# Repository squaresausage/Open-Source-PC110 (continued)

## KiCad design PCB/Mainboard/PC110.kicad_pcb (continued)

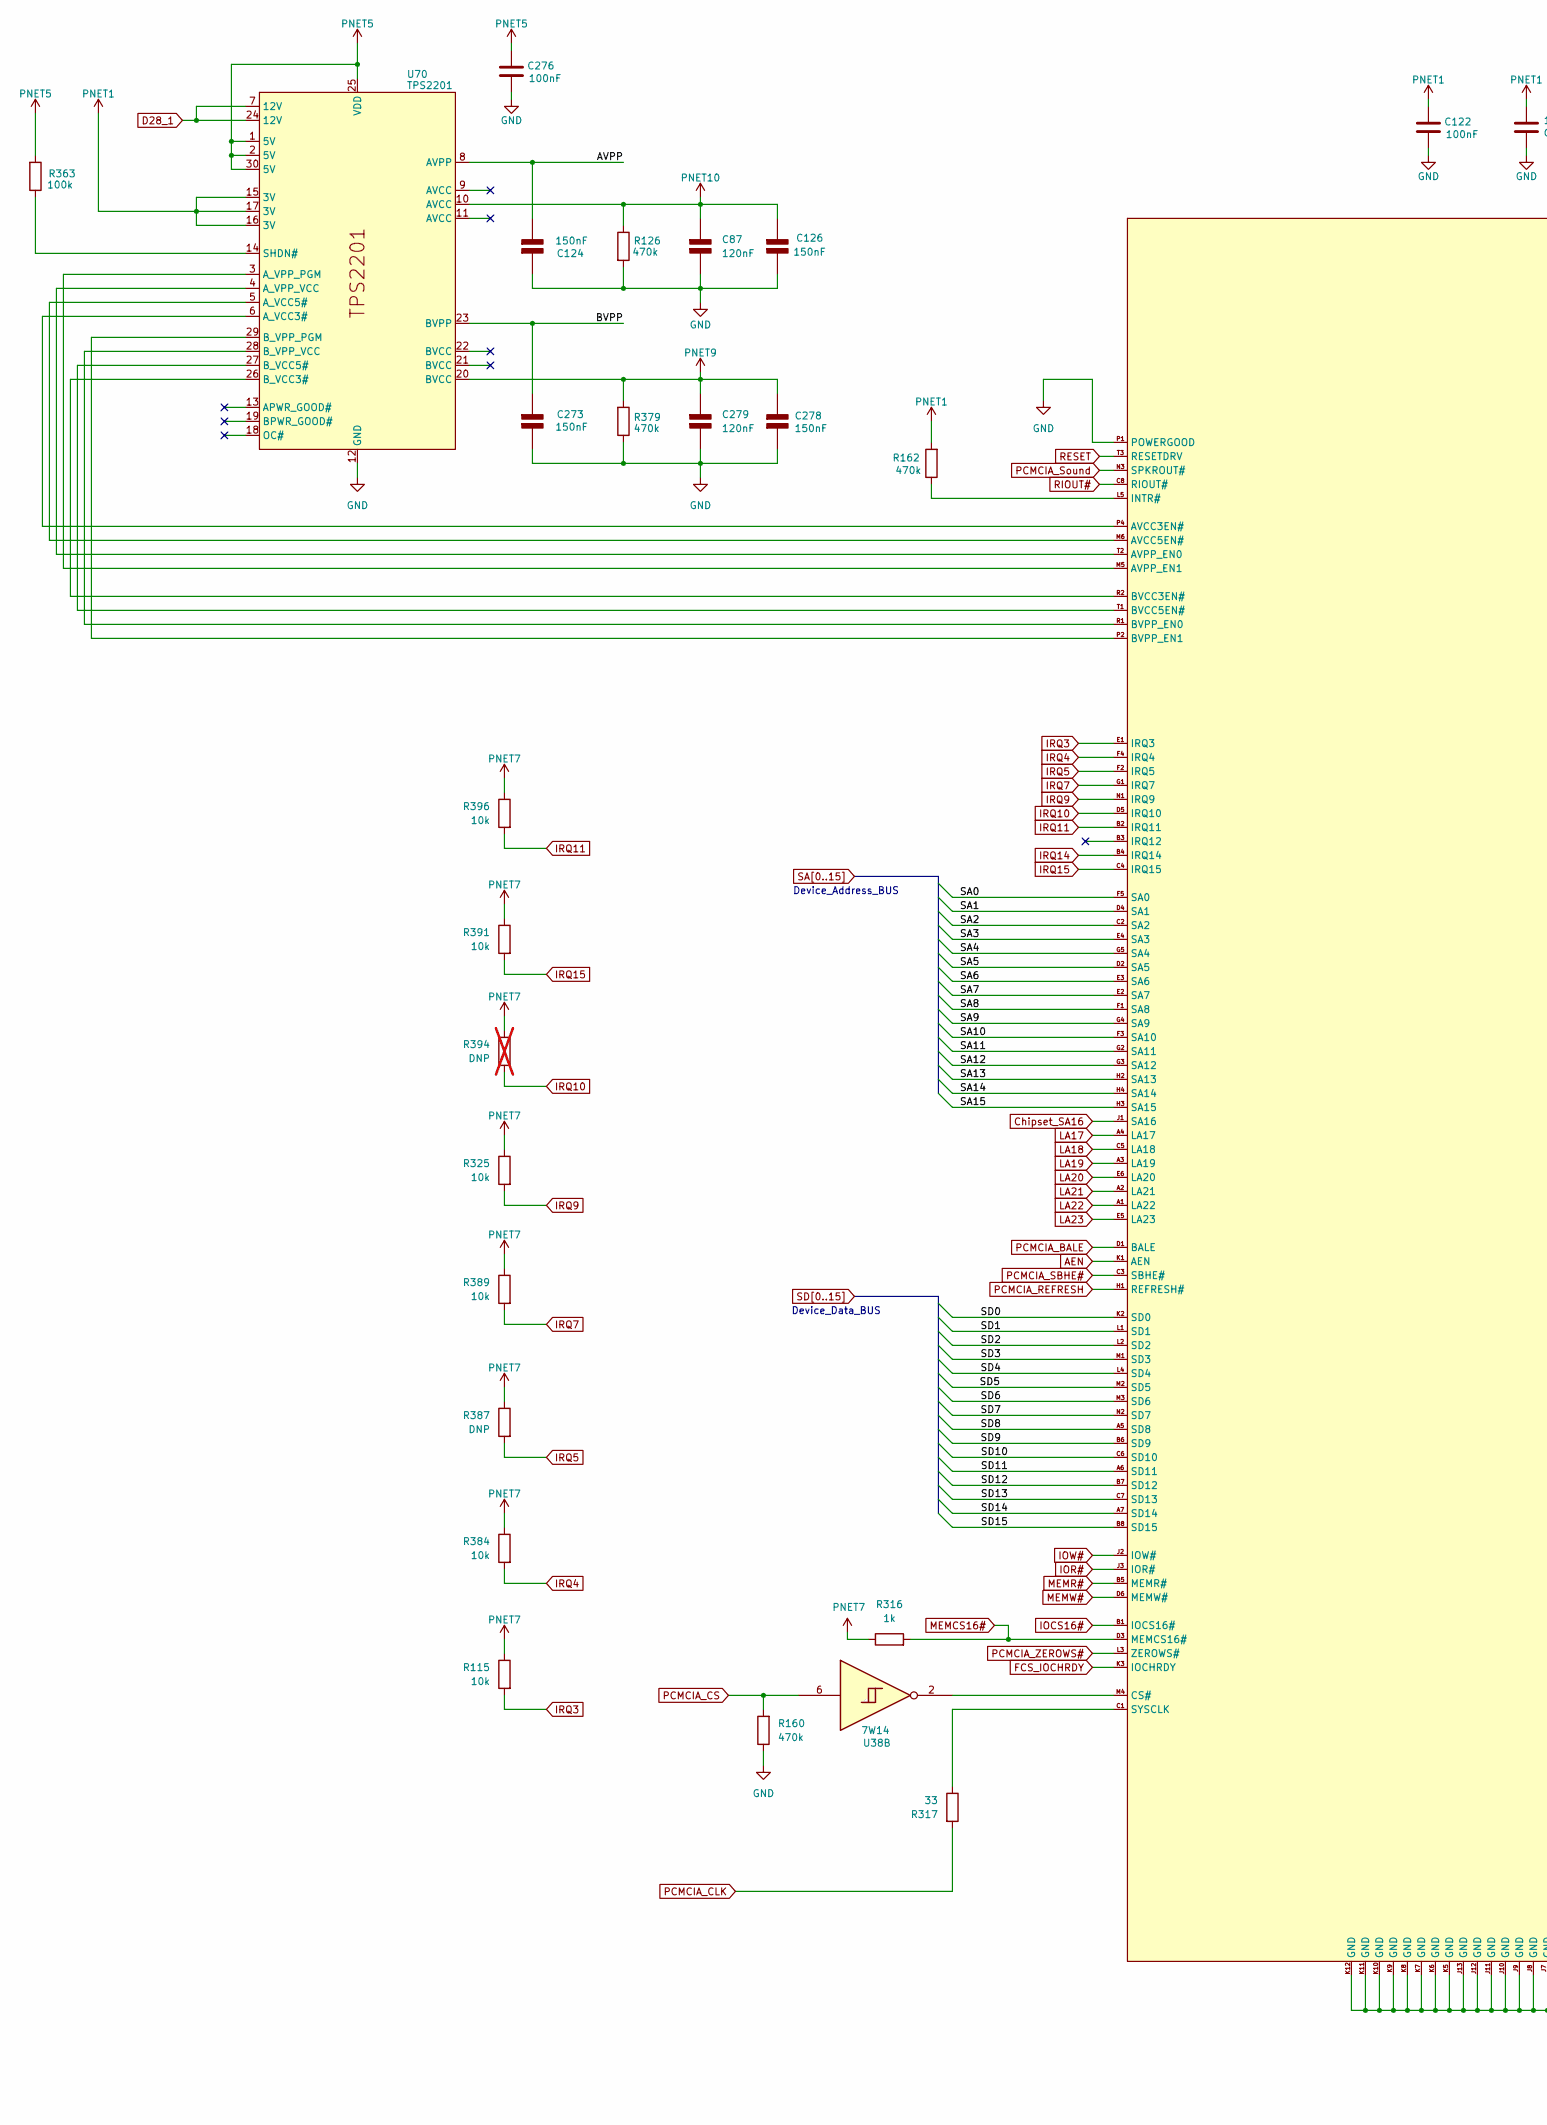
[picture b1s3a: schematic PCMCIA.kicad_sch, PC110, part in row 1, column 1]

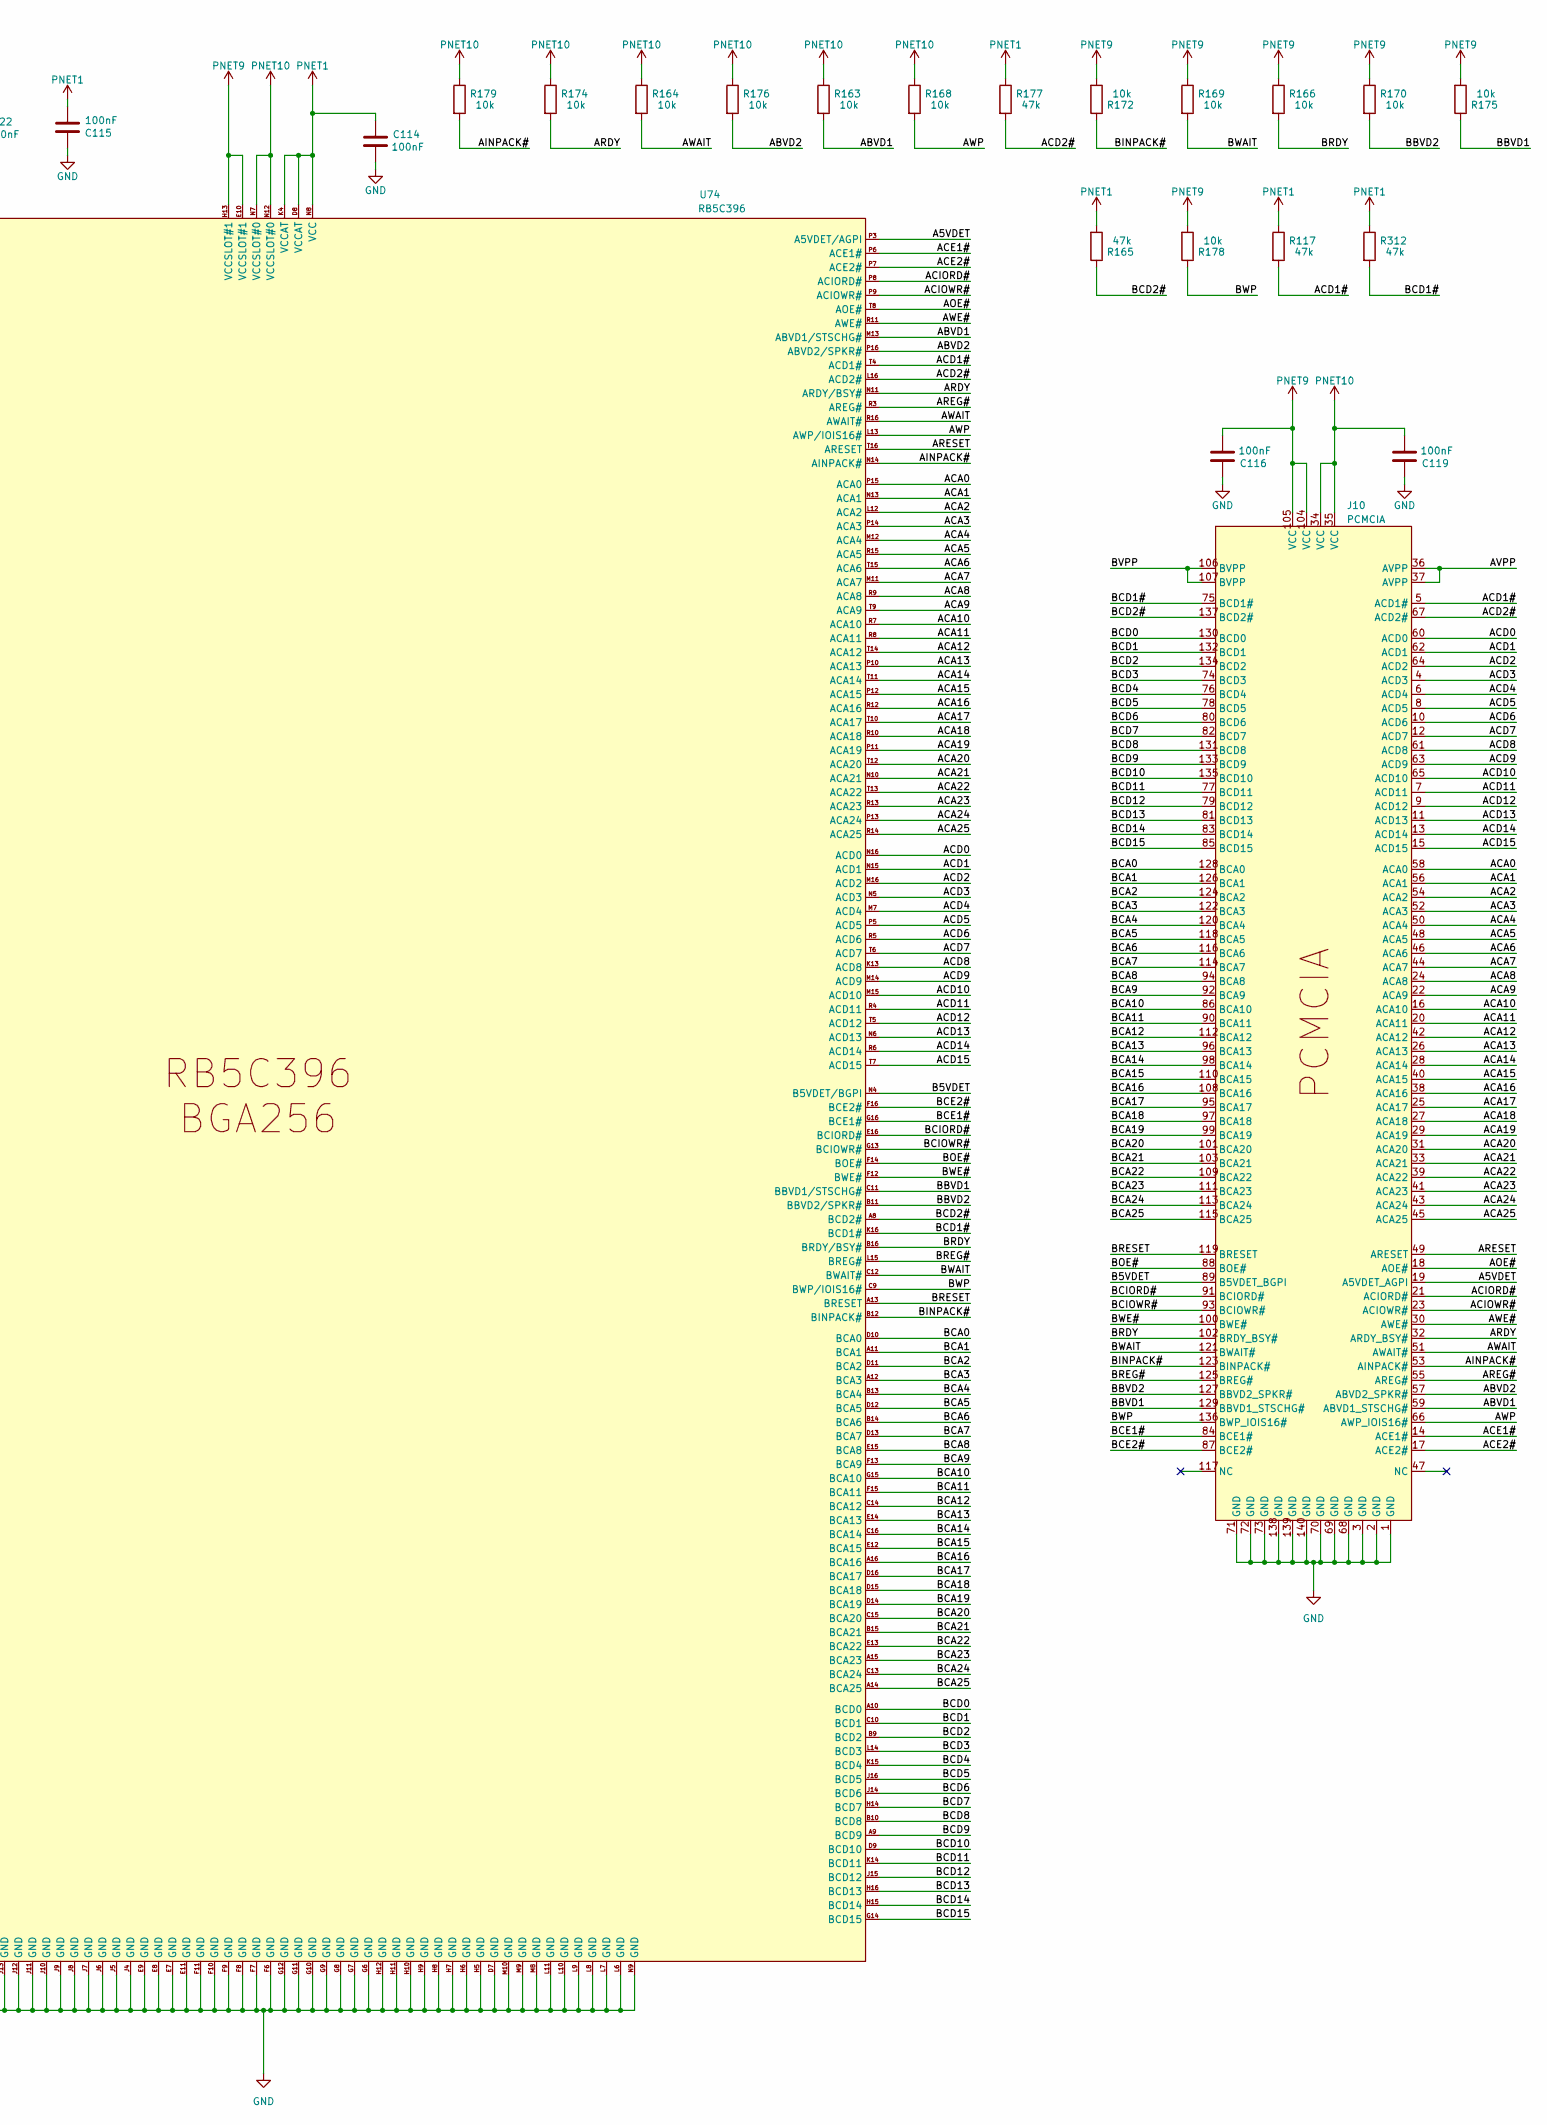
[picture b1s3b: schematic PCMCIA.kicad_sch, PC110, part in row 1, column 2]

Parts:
C87, C279: 120nF; C_0402_1005Metric
C114, C115, C116, C119, C122, C276: 100nF; C_0402_1005Metric
C124, C273: 150nF; C_0603_1608Metric
C126, C278: 150nF; C_0402_1005Metric
J10: PCMCIA
R115, R163, R164, R166, R168, R169, R170, R172, R174, R175, R176, R178, R179, R325, R384, R389, R391, R396: 10k; R_0402_1005Metric
R117, R165, R177, R312: 47k; R_0402_1005Metric
R126, R160, R162, R379: 470k; R_0402_1005Metric
R316: 1k; R_0402_1005Metric
R317: 33; R_0402_1005Metric
R363: 100k; R_0402_1005Metric
R387: DNP; R_0402_1005Metric
R394: DNP; R_0402_1005Metric; not fitted
U38: 7W14; sso-8
U70: TPS2201; TSSOP-30_6.1x9.7mm_P0.65mm
U74: RB5C396; BGA-256

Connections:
/PCMCIA/A5VDET: J10.19 (A5VDET_AGPI), U74.P3 (A5VDET/AGPI)
/PCMCIA/ABVD1: J10.59 (ABVD1_STSCHG#), R163.2, U74.M13 (ABVD1/STSCHG#)
/PCMCIA/ABVD2: J10.57 (ABVD2_SPKR#), R176.2, U74.P16 (ABVD2/SPKR#)
/PCMCIA/ACA0: J10.58 (ACA0), U74.P15 (ACA0)
/PCMCIA/ACA1: J10.56 (ACA1), U74.N13 (ACA1)
/PCMCIA/ACA2: J10.54 (ACA2), U74.L12 (ACA2)
/PCMCIA/ACA3: J10.52 (ACA3), U74.P14 (ACA3)
/PCMCIA/ACA4: J10.50 (ACA4), U74.M12 (ACA4)
/PCMCIA/ACA5: J10.48 (ACA5), U74.R15 (ACA5)
/PCMCIA/ACA6: J10.46 (ACA6), U74.T15 (ACA6)
/PCMCIA/ACA7: J10.44 (ACA7), U74.M11 (ACA7)
/PCMCIA/ACA8: J10.24 (ACA8), U74.R9 (ACA8)
/PCMCIA/ACA9: J10.22 (ACA9), U74.T9 (ACA9)
/PCMCIA/ACA10: J10.16 (ACA10), U74.R7 (ACA10)
/PCMCIA/ACA11: J10.20 (ACA11), U74.R8 (ACA11)
/PCMCIA/ACA12: J10.42 (ACA12), U74.T14 (ACA12)
/PCMCIA/ACA13: J10.26 (ACA13), U74.P10 (ACA13)
/PCMCIA/ACA14: J10.28 (ACA14), U74.T11 (ACA14)
/PCMCIA/ACA15: J10.40 (ACA15), U74.P12 (ACA15)
/PCMCIA/ACA16: J10.38 (ACA16), U74.R12 (ACA16)
/PCMCIA/ACA17: J10.25 (ACA17), U74.T10 (ACA17)
/PCMCIA/ACA18: J10.27 (ACA18), U74.R10 (ACA18)
/PCMCIA/ACA19: J10.29 (ACA19), U74.P11 (ACA19)
/PCMCIA/ACA20: J10.31 (ACA20), U74.T12 (ACA20)
/PCMCIA/ACA21: J10.33 (ACA21), U74.N10 (ACA21)
/PCMCIA/ACA22: J10.39 (ACA22), U74.T13 (ACA22)
/PCMCIA/ACA23: J10.41 (ACA23), U74.R13 (ACA23)
/PCMCIA/ACA24: J10.43 (ACA24), U74.P13 (ACA24)
/PCMCIA/ACA25: J10.45 (ACA25), U74.R14 (ACA25)
/PCMCIA/ACD0: J10.60 (ACD0), U74.N16 (ACD0)
/PCMCIA/ACD1: J10.62 (ACD1), U74.N15 (ACD1)
/PCMCIA/ACD1#: J10.5 (ACD1#), R117.2, U74.T4 (ACD1#)
/PCMCIA/ACD2: J10.64 (ACD2), U74.M16 (ACD2)
/PCMCIA/ACD2#: J10.67 (ACD2#), R177.2, U74.L16 (ACD2#)
/PCMCIA/ACD3: J10.4 (ACD3), U74.N5 (ACD3)
/PCMCIA/ACD4: J10.6 (ACD4), U74.M7 (ACD4)
/PCMCIA/ACD5: J10.8 (ACD5), U74.P5 (ACD5)
/PCMCIA/ACD6: J10.10 (ACD6), U74.R5 (ACD6)
/PCMCIA/ACD7: J10.12 (ACD7), U74.T6 (ACD7)
/PCMCIA/ACD8: J10.61 (ACD8), U74.K13 (ACD8)
/PCMCIA/ACD9: J10.63 (ACD9), U74.M14 (ACD9)
/PCMCIA/ACD10: J10.65 (ACD10), U74.M15 (ACD10)
/PCMCIA/ACD11: J10.7 (ACD11), U74.R4 (ACD11)
/PCMCIA/ACD12: J10.9 (ACD12), U74.T5 (ACD12)
/PCMCIA/ACD13: J10.11 (ACD13), U74.N6 (ACD13)
/PCMCIA/ACD14: J10.13 (ACD14), U74.R6 (ACD14)
/PCMCIA/ACD15: J10.15 (ACD15), U74.T7 (ACD15)
/PCMCIA/ACE1#: J10.14 (ACE1#), U74.P6 (ACE1#)
/PCMCIA/ACE2#: J10.17 (ACE2#), U74.P7 (ACE2#)
/PCMCIA/ACIORD#: J10.21 (ACIORD#), U74.P8 (ACIORD#)
/PCMCIA/ACIOWR#: J10.23 (ACIOWR#), U74.P9 (ACIOWR#)
/PCMCIA/AINPACK#: J10.53 (AINPACK#), R179.2, U74.N14 (AINPACK#)
/PCMCIA/AOE#: J10.18 (AOE#), U74.T8 (AOE#)
/PCMCIA/ARDY: J10.32 (ARDY_BSY#), R174.2, U74.N11 (ARDY/BSY#)
/PCMCIA/AREG#: J10.55 (AREG#), U74.R3 (AREG#)
/PCMCIA/ARESET: J10.49 (ARESET), U74.T16 (ARESET)
/PCMCIA/AVPP: C124.2 (-), J10.36 (AVPP), J10.37 (AVPP), U70.8 (AVPP)
/PCMCIA/AWAIT: J10.51 (AWAIT#), R164.2, U74.R16 (AWAIT#)
/PCMCIA/AWE#: J10.30 (AWE#), U74.R11 (AWE#)
/PCMCIA/AWP: J10.66 (AWP_IOIS16#), R168.2, U74.L13 (AWP/IOIS16#)
/PCMCIA/B5VDET: J10.89 (B5VDET_BGPI), U74.N4 (B5VDET/BGPI)
/PCMCIA/BBVD1: J10.129 (BBVD1_STSCHG#), R175.1, U74.C11 (BBVD1/STSCHG#)
/PCMCIA/BBVD2: J10.127 (BBVD2_SPKR#), R170.2, U74.B11 (BBVD2/SPKR#)
/PCMCIA/BCA0: J10.128 (BCA0), U74.D10 (BCA0)
/PCMCIA/BCA1: J10.126 (BCA1), U74.A11 (BCA1)
/PCMCIA/BCA2: J10.124 (BCA2), U74.D11 (BCA2)
/PCMCIA/BCA3: J10.122 (BCA3), U74.A12 (BCA3)
/PCMCIA/BCA4: J10.120 (BCA4), U74.B13 (BCA4)
/PCMCIA/BCA5: J10.118 (BCA5), U74.D12 (BCA5)
/PCMCIA/BCA6: J10.116 (BCA6), U74.B14 (BCA6)
/PCMCIA/BCA7: J10.114 (BCA7), U74.D13 (BCA7)
/PCMCIA/BCA8: J10.94 (BCA8), U74.E15 (BCA8)
/PCMCIA/BCA9: J10.92 (BCA9), U74.F13 (BCA9)
/PCMCIA/BCA10: J10.86 (BCA10), U74.G15 (BCA10)
/PCMCIA/BCA11: J10.90 (BCA11), U74.F15 (BCA11)
/PCMCIA/BCA12: J10.112 (BCA12), U74.C14 (BCA12)
/PCMCIA/BCA13: J10.96 (BCA13), U74.E14 (BCA13)
/PCMCIA/BCA14: J10.98 (BCA14), U74.C16 (BCA14)
/PCMCIA/BCA15: J10.110 (BCA15), U74.E12 (BCA15)
/PCMCIA/BCA16: J10.108 (BCA16), U74.A16 (BCA16)
/PCMCIA/BCA17: J10.95 (BCA17), U74.D16 (BCA17)
/PCMCIA/BCA18: J10.97 (BCA18), U74.D15 (BCA18)
/PCMCIA/BCA19: J10.99 (BCA19), U74.D14 (BCA19)
/PCMCIA/BCA20: J10.101 (BCA20), U74.C15 (BCA20)
/PCMCIA/BCA21: J10.103 (BCA21), U74.B15 (BCA21)
/PCMCIA/BCA22: J10.109 (BCA22), U74.E13 (BCA22)
/PCMCIA/BCA23: J10.111 (BCA23), U74.A15 (BCA23)
/PCMCIA/BCA24: J10.113 (BCA24), U74.C13 (BCA24)
/PCMCIA/BCA25: J10.115 (BCA25), U74.A14 (BCA25)
/PCMCIA/BCD0: J10.130 (BCD0), U74.A10 (BCD0)
/PCMCIA/BCD1: J10.132 (BCD1), U74.C10 (BCD1)
/PCMCIA/BCD1#: J10.75 (BCD1#), R312.2, U74.K16 (BCD1#)
/PCMCIA/BCD2: J10.134 (BCD2), U74.B9 (BCD2)
/PCMCIA/BCD2#: J10.137 (BCD2#), R165.1, U74.A8 (BCD2#)
/PCMCIA/BCD3: J10.74 (BCD3), U74.L14 (BCD3)
/PCMCIA/BCD4: J10.76 (BCD4), U74.K15 (BCD4)
/PCMCIA/BCD5: J10.78 (BCD5), U74.J16 (BCD5)
/PCMCIA/BCD6: J10.80 (BCD6), U74.J14 (BCD6)
/PCMCIA/BCD7: J10.82 (BCD7), U74.H14 (BCD7)
/PCMCIA/BCD8: J10.131 (BCD8), U74.B10 (BCD8)
/PCMCIA/BCD9: J10.133 (BCD9), U74.A9 (BCD9)
/PCMCIA/BCD10: J10.135 (BCD10), U74.D9 (BCD10)
/PCMCIA/BCD11: J10.77 (BCD11), U74.K14 (BCD11)
/PCMCIA/BCD12: J10.79 (BCD12), U74.J15 (BCD12)
/PCMCIA/BCD13: J10.81 (BCD13), U74.H16 (BCD13)
/PCMCIA/BCD14: J10.83 (BCD14), U74.H15 (BCD14)
/PCMCIA/BCD15: J10.85 (BCD15), U74.G14 (BCD15)
/PCMCIA/BCE1#: J10.84 (BCE1#), U74.G16 (BCE1#)
/PCMCIA/BCE2#: J10.87 (BCE2#), U74.F16 (BCE2#)
/PCMCIA/BCIORD#: J10.91 (BCIORD#), U74.E16 (BCIORD#)
/PCMCIA/BCIOWR#: J10.93 (BCIOWR#), U74.G13 (BCIOWR#)
/PCMCIA/BINPACK#: J10.123 (BINPACK#), R172.1, U74.B12 (BINPACK#)
/PCMCIA/BOE#: J10.88 (BOE#), U74.F14 (BOE#)
/PCMCIA/BRDY: J10.102 (BRDY_BSY#), R166.2, U74.B16 (BRDY/BSY#)
/PCMCIA/BREG#: J10.125 (BREG#), U74.L15 (BREG#)
/PCMCIA/BRESET: J10.119 (BRESET), U74.A13 (BRESET)
/PCMCIA/BVPP: C273.1 (+), J10.106 (BVPP), J10.107 (BVPP), U70.23 (BVPP)
/PCMCIA/BWAIT: J10.121 (BWAIT#), R169.2, U74.C12 (BWAIT#)
/PCMCIA/BWE#: J10.100 (BWE#), U74.F12 (BWE#)
/PCMCIA/BWP: J10.136 (BWP_IOIS16#), R178.1, U74.C9 (BWP/IOIS16#)
AEN: U74.K1 (AEN); also elsewhere on the board
Chipset_SA16: U74.J1 (SA16); also elsewhere on the board
D28_1: U70.7 (12V), U70.24 (12V); also elsewhere on the board
FCS_IOCHRDY: U74.K3 (IOCHRDY); also elsewhere on the board
IOCS16#: U74.B1 (IOCS16#); also elsewhere on the board
IOR#: U74.J3 (IOR#); also elsewhere on the board
IOW#: U74.J2 (IOW#); also elsewhere on the board
IRQ3: R115.2, U74.E1 (IRQ3); also elsewhere on the board
IRQ4: R384.2, U74.F4 (IRQ4); also elsewhere on the board
IRQ5: R387.2, U74.F2 (IRQ5); also elsewhere on the board
IRQ7: R389.2, U74.G1 (IRQ7); also elsewhere on the board
IRQ9: R325.2, U74.N1 (IRQ9); also elsewhere on the board
IRQ10: R394.2, U74.D5 (IRQ10); also elsewhere on the board
IRQ11: R396.2, U74.B2 (IRQ11); also elsewhere on the board
IRQ14: U74.B4 (IRQ14); also elsewhere on the board
IRQ15: R391.2, U74.C4 (IRQ15); also elsewhere on the board
LA17: U74.A4 (LA17); also elsewhere on the board
LA18: U74.C5 (LA18); also elsewhere on the board
LA19: U74.A3 (LA19); also elsewhere on the board
LA20: U74.E6 (LA20); also elsewhere on the board
LA21: U74.A2 (LA21); also elsewhere on the board
LA22: U74.A1 (LA22); also elsewhere on the board
LA23: U74.E5 (LA23); also elsewhere on the board
MEMCS16#: R316.2, U74.D3 (MEMCS16#); also elsewhere on the board
MEMR#: U74.B5 (MEMR#); also elsewhere on the board
MEMW#: U74.D6 (MEMW#); also elsewhere on the board
unnamed: U70.6 (A_VCC3#), U74.P4 (AVCC3EN#)
unnamed: U70.5 (A_VCC5#), U74.M6 (AVCC5EN#)
unnamed: U70.3 (A_VPP_PGM), U74.M5 (AVPP_EN1)
unnamed: U70.4 (A_VPP_VCC), U74.T2 (AVPP_EN0)
unnamed: U70.26 (B_VCC3#), U74.R2 (BVCC3EN#)
unnamed: U70.27 (B_VCC5#), U74.T1 (BVCC5EN#)
unnamed: U70.29 (B_VPP_PGM), U74.P2 (BVPP_EN1)
unnamed: U70.28 (B_VPP_VCC), U74.R1 (BVPP_EN0)
unnamed: R363.1, U70.14 (SHDN#)
unnamed: U38.2, U74.M4 (CS#)
unnamed: R162.1, U74.L5 (INTR#)
unnamed: R317.1, U74.C1 (SYSCLK)
PCMCIA_BALE: U74.D1 (BALE); also elsewhere on the board
PCMCIA_CLK: R317.2; also elsewhere on the board
PCMCIA_CS: R160.2, U38.6; also elsewhere on the board
PCMCIA_REFRESH: U74.H1 (REFRESH#); also elsewhere on the board
PCMCIA_SBHE#: U74.C3 (SBHE#); also elsewhere on the board
PCMCIA_Sound: U74.N3 (SPKROUT#); also elsewhere on the board
PCMCIA_ZEROWS#: U74.L3 (ZEROWS#); also elsewhere on the board
PNET1: C114.2, C115.2, C122.1, R117.1, R162.2, R165.2, R177.1, R312.1, U70.15 (3V), U70.16 (3V), U70.17 (3V), U74.D8 (VCCAT), U74.K4 (VCCAT), U74.N8 (VCC); also elsewhere on the board
PNET7: R115.1, R316.1, R325.1, R384.1, R387.1, R389.1, R391.1, R394.1, R396.1; also elsewhere on the board
PNET9: C116.1, C278.2 (-), C279.1 (+), J10.104 (VCC), J10.105 (VCC), R166.1, R169.1, R170.1, R172.2, R175.2, R178.2, R379.2, U70.20 (BVCC), U74.E10 (VCCSLOT#1), U74.H13 (VCCSLOT#1)
PNET10: C87.1 (+), C119.1, C126.1 (+), J10.34 (VCC), J10.35 (VCC), R126.1, R163.1, R164.1, R168.1, R174.1, R176.1, R179.1, U70.10 (AVCC), U74.N7 (VCCSLOT#0), U74.N12 (VCCSLOT#0)
RESET: U74.T3 (RESETDRV); also elsewhere on the board
RIOUT#: U74.C8 (RIOUT#); also elsewhere on the board
SA0: U74.F5 (SA0); also elsewhere on the board
SA1: U74.D4 (SA1); also elsewhere on the board
SA2: U74.C2 (SA2); also elsewhere on the board
SA3: U74.E4 (SA3); also elsewhere on the board
SA4: U74.G5 (SA4); also elsewhere on the board
SA5: U74.D2 (SA5); also elsewhere on the board
SA6: U74.E3 (SA6); also elsewhere on the board
SA7: U74.E2 (SA7); also elsewhere on the board
SA8: U74.F1 (SA8); also elsewhere on the board
SA9: U74.G4 (SA9); also elsewhere on the board
SA10: U74.F3 (SA10); also elsewhere on the board
SA11: U74.G2 (SA11); also elsewhere on the board
SA12: U74.G3 (SA12); also elsewhere on the board
SA13: U74.H2 (SA13); also elsewhere on the board
SA14: U74.H4 (SA14); also elsewhere on the board
SA15: U74.H3 (SA15); also elsewhere on the board
SD0: U74.K2 (SD0); also elsewhere on the board
SD1: U74.L1 (SD1); also elsewhere on the board
SD2: U74.L2 (SD2); also elsewhere on the board
SD3: U74.M1 (SD3); also elsewhere on the board
SD4: U74.L4 (SD4); also elsewhere on the board
SD5: U74.M2 (SD5); also elsewhere on the board
SD6: U74.M3 (SD6); also elsewhere on the board
SD7: U74.N2 (SD7); also elsewhere on the board
SD8: U74.A5 (SD8); also elsewhere on the board
SD9: U74.B6 (SD9); also elsewhere on the board
SD10: U74.C6 (SD10); also elsewhere on the board
SD11: U74.A6 (SD11); also elsewhere on the board
SD12: U74.B7 (SD12); also elsewhere on the board
SD13: U74.C7 (SD13); also elsewhere on the board
SD14: U74.A7 (SD14); also elsewhere on the board
SD15: U74.B8 (SD15); also elsewhere on the board

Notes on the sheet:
Device_Data_BUS
Device_Address_BUS

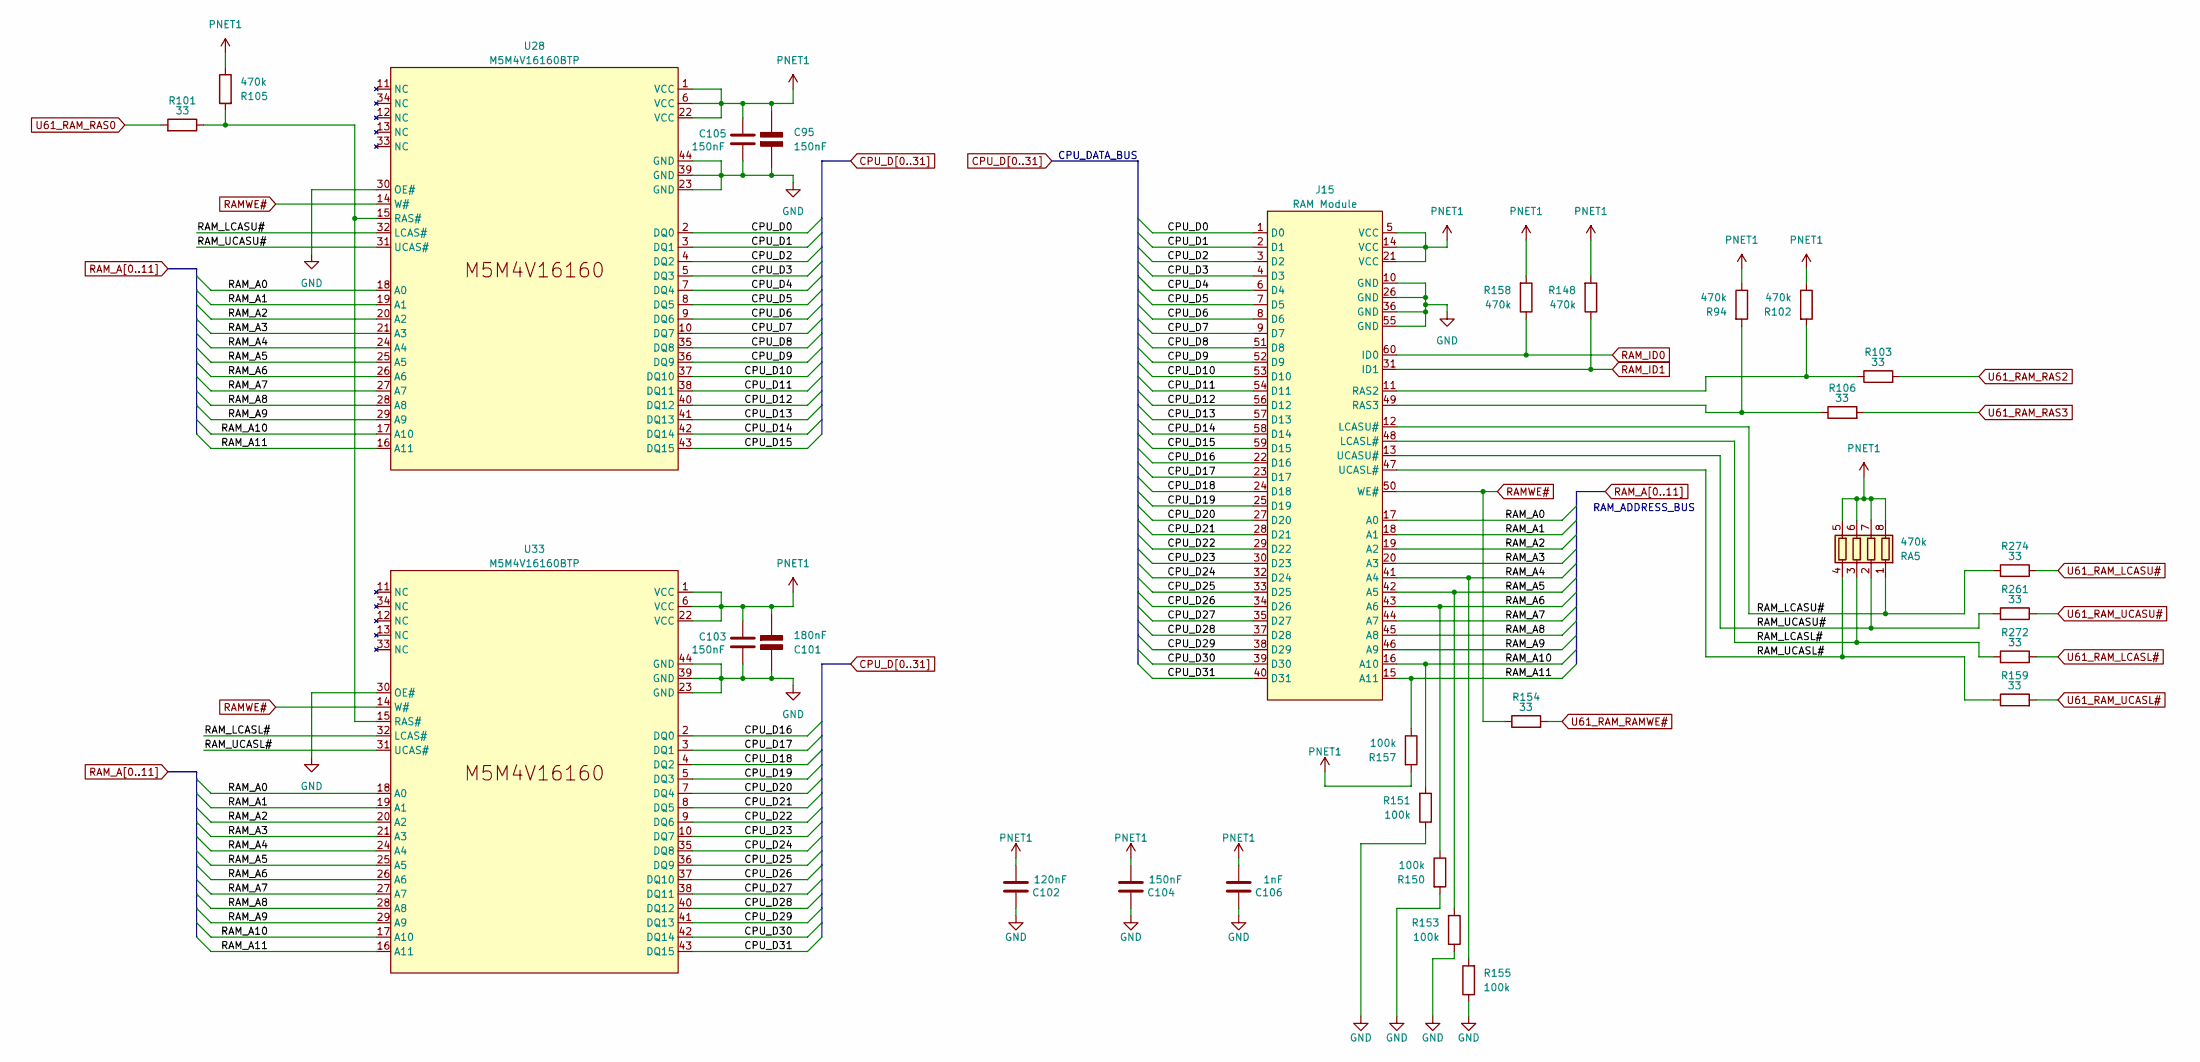
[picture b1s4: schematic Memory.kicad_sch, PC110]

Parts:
C95, C103, C104, C105: 150nF; C_0402_1005Metric
C101: 180nF; C_0402_1005Metric
C102: 120nF; C_0402_1005Metric
C106: 1nF; C_0402_1005Metric
J15: RAM Module
R94, R102, R105, R148, R158: 470k; R_0402_1005Metric
R101, R103, R106, R154, R159, R261, R272, R274: 33; R_0402_1005Metric
R150, R151, R153, R155, R157: 100k; R_0402_1005Metric
RA5: 470k; R-array
U28, U33: M5M4V16160BTP; RAMchip

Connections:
/Memory/RAM_LCASL#: J15.48 (LCASL#), R272.2, RA5.3 (R3.1), U33.32 (LCAS#)
/Memory/RAM_LCASU#: J15.12 (LCASU#), R274.2, RA5.1 (R1.1), U28.32 (LCAS#)
/Memory/RAM_UCASL#: J15.47 (UCASL#), R159.1, RA5.4 (R4.1), U33.31 (UCAS#)
/Memory/RAM_UCASU#: J15.13 (UCASU#), R261.2, RA5.2 (R2.1), U28.31 (UCAS#)
CPU_D0: J15.1 (D0), U28.2 (DQ0); also elsewhere on the board
CPU_D1: J15.2 (D1), U28.3 (DQ1); also elsewhere on the board
CPU_D2: J15.3 (D2), U28.4 (DQ2); also elsewhere on the board
CPU_D3: J15.4 (D3), U28.5 (DQ3); also elsewhere on the board
CPU_D4: J15.6 (D4), U28.7 (DQ4); also elsewhere on the board
CPU_D5: J15.7 (D5), U28.8 (DQ5); also elsewhere on the board
CPU_D6: J15.8 (D6), U28.9 (DQ6); also elsewhere on the board
CPU_D7: J15.9 (D7), U28.10 (DQ7); also elsewhere on the board
CPU_D8: J15.51 (D8), U28.35 (DQ8); also elsewhere on the board
CPU_D9: J15.52 (D9), U28.36 (DQ9); also elsewhere on the board
CPU_D10: J15.53 (D10), U28.37 (DQ10); also elsewhere on the board
CPU_D11: J15.54 (D11), U28.38 (DQ11); also elsewhere on the board
CPU_D12: J15.56 (D12), U28.40 (DQ12); also elsewhere on the board
CPU_D13: J15.57 (D13), U28.41 (DQ13); also elsewhere on the board
CPU_D14: J15.58 (D14), U28.42 (DQ14); also elsewhere on the board
CPU_D15: J15.59 (D15), U28.43 (DQ15); also elsewhere on the board
CPU_D16: J15.22 (D16), U33.2 (DQ0); also elsewhere on the board
CPU_D17: J15.23 (D17), U33.3 (DQ1); also elsewhere on the board
CPU_D18: J15.24 (D18), U33.4 (DQ2); also elsewhere on the board
CPU_D19: J15.25 (D19), U33.5 (DQ3); also elsewhere on the board
CPU_D20: J15.27 (D20), U33.7 (DQ4); also elsewhere on the board
CPU_D21: J15.28 (D21), U33.8 (DQ5); also elsewhere on the board
CPU_D22: J15.29 (D22), U33.9 (DQ6); also elsewhere on the board
CPU_D23: J15.30 (D23), U33.10 (DQ7); also elsewhere on the board
CPU_D24: J15.32 (D24), U33.35 (DQ8); also elsewhere on the board
CPU_D25: J15.33 (D25), U33.36 (DQ9); also elsewhere on the board
CPU_D26: J15.34 (D26), U33.37 (DQ10); also elsewhere on the board
CPU_D27: J15.35 (D27), U33.38 (DQ11); also elsewhere on the board
CPU_D28: J15.37 (D28), U33.40 (DQ12); also elsewhere on the board
CPU_D29: J15.38 (D29), U33.41 (DQ13); also elsewhere on the board
CPU_D30: J15.39 (D30), U33.42 (DQ14); also elsewhere on the board
CPU_D31: J15.40 (D31), U33.43 (DQ15); also elsewhere on the board
unnamed: J15.11 (RAS2), R102.2, R103.1
unnamed: J15.49 (RAS3), R94.2, R106.1
unnamed: R101.1, R105.2, U28.15 (RAS#), U33.15 (RAS#)
PNET1: C95.1 (+), C101.2 (-), C102.2, C103.1, C104.2, C105.1, C106.2, J15.5 (VCC), J15.14 (VCC), J15.21 (VCC), R94.1, R102.1, R105.1, R148.2, R157.2, R158.2, RA5.5 (R4.2), RA5.6 (R3.2), RA5.7 (R2.2), RA5.8 (R1.2), U28.1 (VCC), U28.6 (VCC), U28.22 (VCC), U33.1 (VCC), U33.6 (VCC), U33.22 (VCC); also elsewhere on the board
RAMWE#: J15.50 (WE#), R154.1, U28.14 (W#), U33.14 (W#)
RAM_A0: J15.17 (A0), U28.18 (A0), U33.18 (A0); also elsewhere on the board
RAM_A1: J15.18 (A1), U28.19 (A1), U33.19 (A1); also elsewhere on the board
RAM_A2: J15.19 (A2), U28.20 (A2), U33.20 (A2); also elsewhere on the board
RAM_A3: J15.20 (A3), U28.21 (A3), U33.21 (A3); also elsewhere on the board
RAM_A4: J15.41 (A4), R155.2, U28.24 (A4), U33.24 (A4); also elsewhere on the board
RAM_A5: J15.42 (A5), R153.2, U28.25 (A5), U33.25 (A5); also elsewhere on the board
RAM_A6: J15.43 (A6), R150.1, U28.26 (A6), U33.26 (A6); also elsewhere on the board
RAM_A7: J15.44 (A7), U28.27 (A7), U33.27 (A7); also elsewhere on the board
RAM_A8: J15.45 (A8), U28.28 (A8), U33.28 (A8); also elsewhere on the board
RAM_A9: J15.46 (A9), U28.29 (A9), U33.29 (A9); also elsewhere on the board
RAM_A10: J15.16 (A10), R151.2, U28.17 (A10), U33.17 (A10); also elsewhere on the board
RAM_A11: J15.15 (A11), R157.1, U28.16 (A11), U33.16 (A11); also elsewhere on the board
U61_RAM_LCASL#: R272.1; also elsewhere on the board
U61_RAM_LCASU#: R274.1; also elsewhere on the board
U61_RAM_RAMWE#: R154.2; also elsewhere on the board
U61_RAM_RAS0: R101.2; also elsewhere on the board
U61_RAM_RAS2: R103.2; also elsewhere on the board
U61_RAM_RAS3: R106.2; also elsewhere on the board
U61_RAM_UCASL#: R159.2; also elsewhere on the board
U61_RAM_UCASU#: R261.1; also elsewhere on the board

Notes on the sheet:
RAM_ADDRESS_BUS
CPU_DATA_BUS
